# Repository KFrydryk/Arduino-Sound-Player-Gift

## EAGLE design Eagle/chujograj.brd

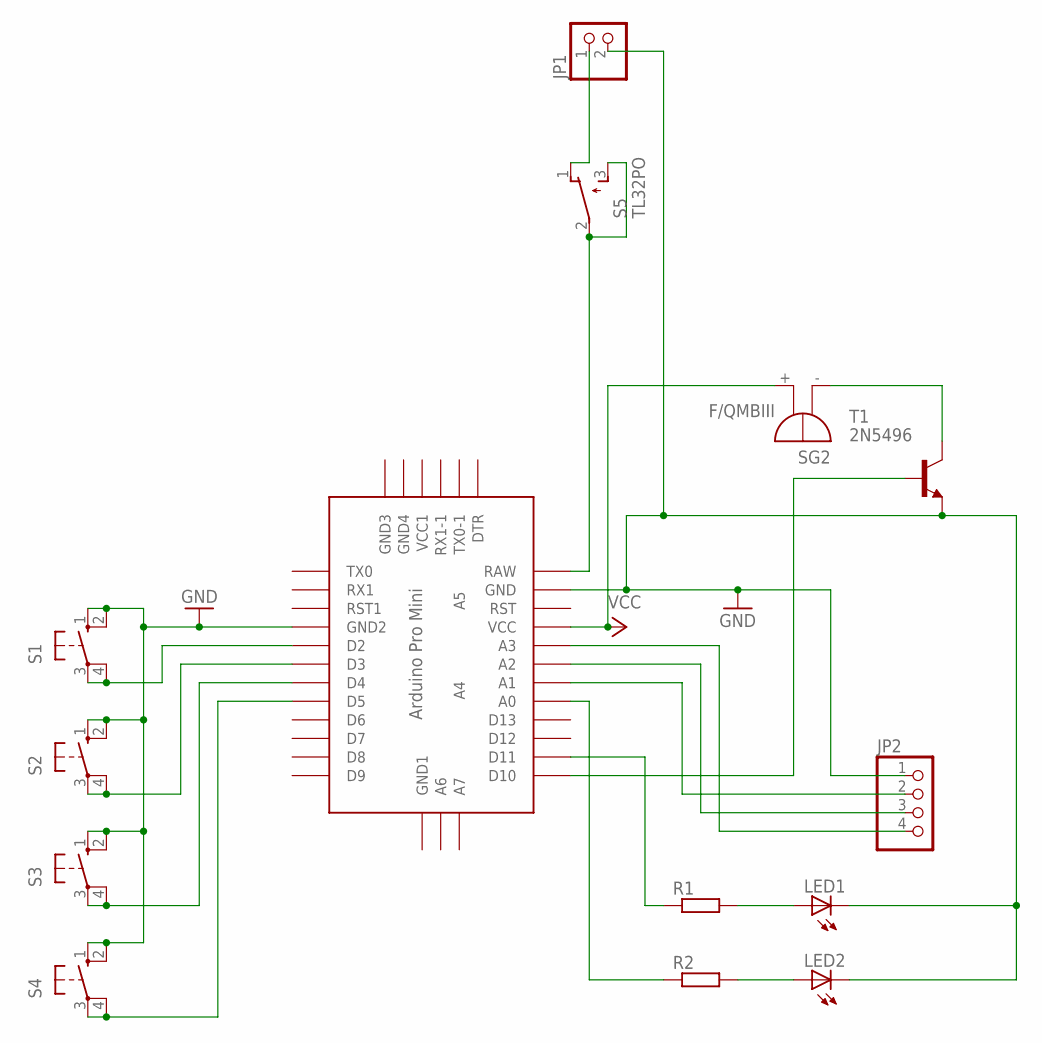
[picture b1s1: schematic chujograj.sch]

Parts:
JP1: PINHD-1X2; 1X02
JP2: PINHD-1X4; 1X04
LED1, LED2: LED5MM
R1, R2: R-EU_0207/10; 0207/10
S1, S2, S3, S4: 40-XX; B3F-40XX
S5: TL32PO; TL3XPO
SG2: F/QMBIII
T1: 2N5496; TO220
U$1: ABK-PRO-MINI

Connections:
GND: JP1.2, JP2.1, LED1.K (C), LED2.K (C), S1.1 (S), S1.2 (S1), S2.1 (S), S2.2 (S1), S3.1 (S), S3.2 (S1), S4.1 (S), S4.2 (S1), T1.3 (E), U$1.GND, U$1.GND1 (GND2)
unnamed: S1.3, S1.4 (P1), U$1.D2
unnamed: S2.3, S2.4 (P1), U$1.D3
unnamed: S3.3, S3.4 (P1), U$1.D4
unnamed: S4.3, S4.4 (P1), U$1.D5
unnamed: SG2.- (+), T1.2 (C)
unnamed: T1.1 (B), U$1.D10
unnamed: JP2.2, U$1.A1
unnamed: JP2.3, U$1.A2
unnamed: JP2.4, U$1.A3
unnamed: R1.1, U$1.D11
unnamed: R2.1, U$1.A0
unnamed: LED2.A, R2.2
unnamed: LED1.A, R1.2
unnamed: S5.2, S5.3 (S), U$1.RAW
unnamed: JP1.1, S5.1 (O)
VCC: SG2.+ (-), U$1.VCC

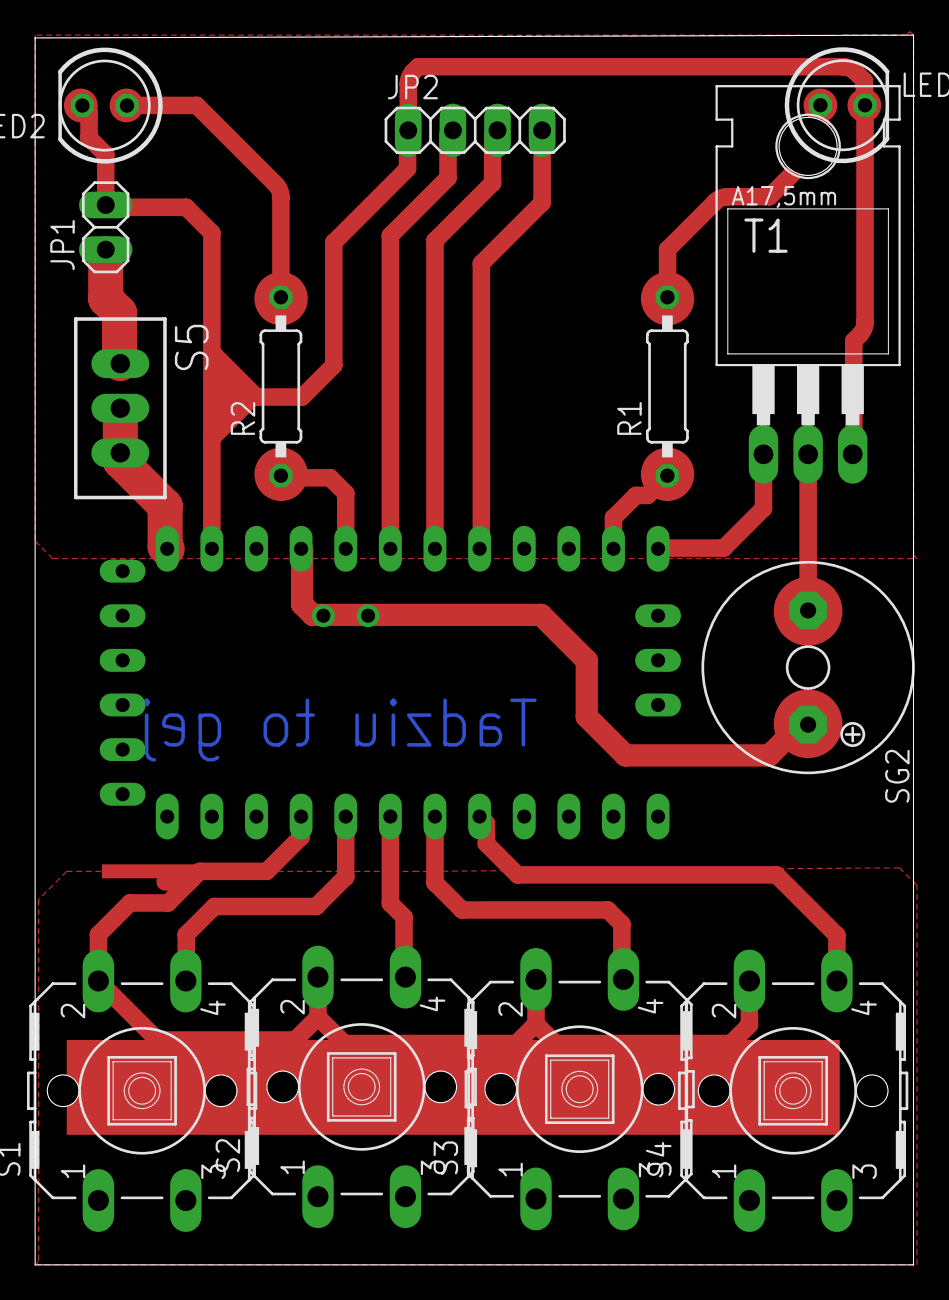
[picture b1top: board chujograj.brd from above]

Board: 2 copper layers, 50.0 x 70.0 mm, 14 parts (0 on the bottom side), 17 nets.

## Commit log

2020-04-19 first and last commit - it's only a backup
